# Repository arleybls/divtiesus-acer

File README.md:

# divtiesus-acer

A custom-PCB fork of **DivTIESUS** — a DivMMC-compatible SD/MMC card interface for the ZX Spectrum.

This fork is a **board re-layout only**: the CPLD firmware and its pinout are unchanged from
upstream, so the existing logic runs on the new PCB without modification.

## Lineage

| Stage | Author | Repo |
|-------|--------|------|
| Original DivTIESUS | Miguel Ángel Rodríguez Jodar (*mcleod-ideafix*) | https://github.com/mcleod-ideafix/divtiesus |
| KiCad redesign ("maple" edition) | anarsoul | https://github.com/anarsoul/divtiesus_maple |
| This fork (`divtiesus-acer`) | — | custom PCB re-layout based on the maple edition |

## What is unchanged from upstream

The entire `cpld/` directory matches the maple edition:

- Same Verilog sources: `tld_divtiesus.v`, `divmmc_mcleod.v`, `modo.v`, `segajoy.v`, `tres_e.v`,
  `uart.v`, `zxunoregs.v`, `zxunouart.v`
- Same `config.vh` and `Makefile`
- Same `tld_divtiesus.qsf` pin map — target device **Altera MAX II `EPM240T100C5`**

Inherited feature set:

- DivMMC-compatible interface with 8 KiB EEPROM and 128 KiB or 512 KiB RAM
- Automatic Spectrum model detection (no jumpers/switches)
- 24 MHz independent clock
- microSD card support with activity LED
- NMI and RESET buttons (file browser access)
- Optional ZX-Uno-compatible UART for WiFi (115200 baud)
- Kempston joystick interface (Atari and Sega controllers)
- Soft +3E feature removed (as in the maple edition)

## License

GPLv3, inherited from the upstream sources (see the GPL headers in `cpld/tld_divtiesus.v` and the
ZX-Uno notice in `cpld/config.vh`).

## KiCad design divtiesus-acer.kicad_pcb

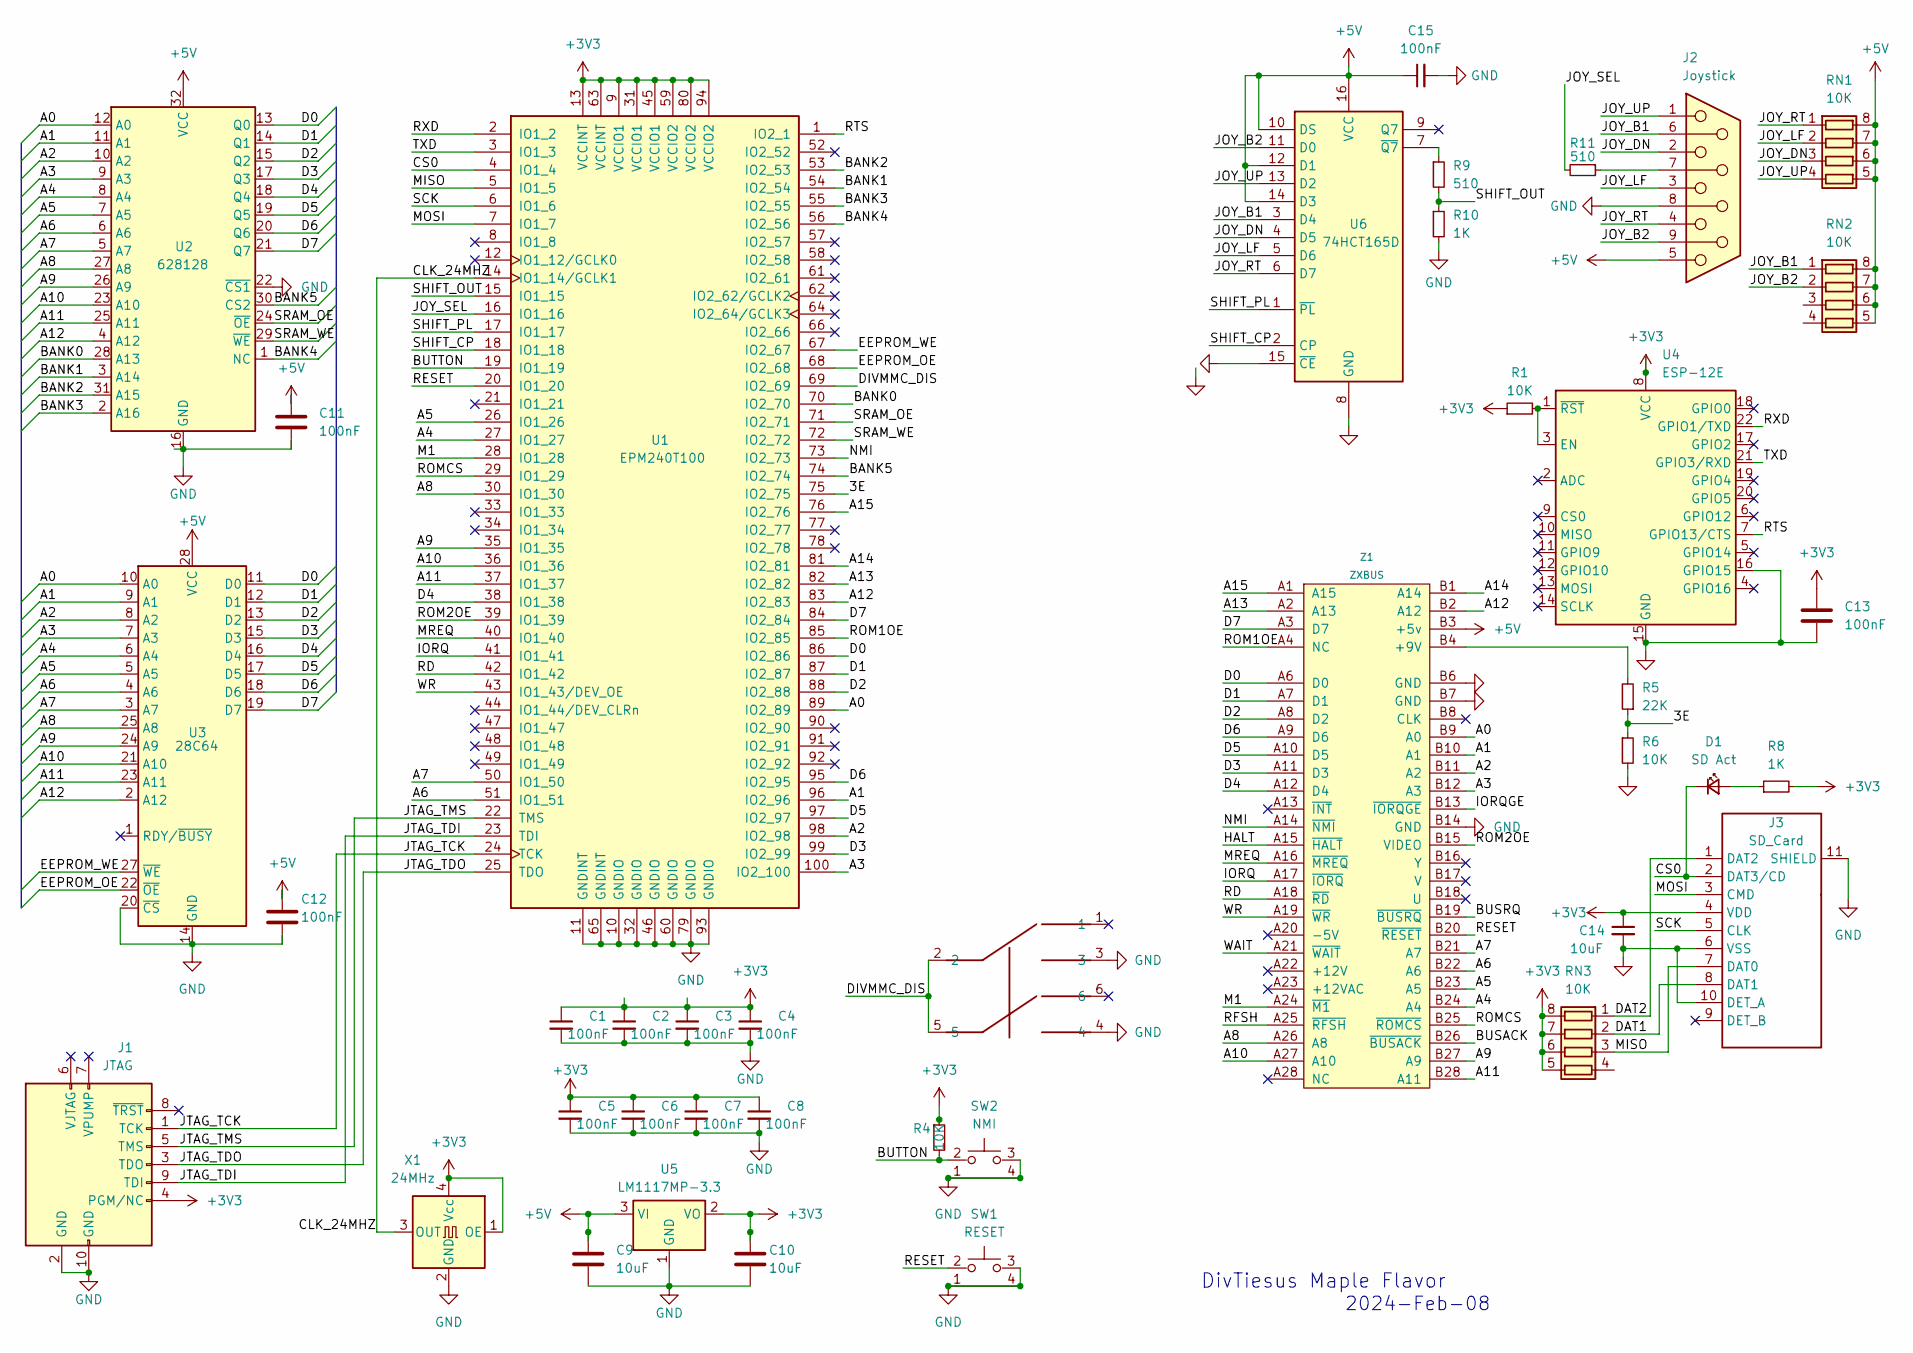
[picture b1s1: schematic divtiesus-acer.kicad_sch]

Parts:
C1, C2, C3, C4, C5, C6, C7, C8, C11, C12, C13, C15: 100nF; C_0603_1608Metric
C9, C10, C14: 10uF; C_0805_2012Metric
D1: SD Act; LED_0805_2012Metric
J1: JTAG; IDC-Header_2x05_P2.54mm_Vertical
J2: Joystick; DSUB-9_Male_Horizontal_P2.77x2.84mm_EdgePinOffset9.90mm_Hou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
J3: SD_Card; microSD_HC_Hirose_DM3D-SF; PARTREV AX6
JUMPER_E2: SWITCH_SMD_6PIN; SWICTH_SMD_6P
R1, R4, R6: 10K; R_0603_1608Metric
R5: 22K; R_0603_1608Metric
R8, R10: 1K; R_0603_1608Metric
R9, R11: 510; R_0603_1608Metric
RN1, RN2, RN3: 10K; R_Array_Convex_4x0603
SW1: RESET; SW_Tactile_SPST_Angled_PTS645Vx58-2LFS
SW2: NMI; SW_Tactile_SPST_Angled_PTS645Vx58-2LFS
U1: EPM240T100; TQFP-100_14x14mm_P0.5mm
U2: 628128; SSOP-32_11.305x20.495mm_P1.27mm
U3: 28C64; SOIC-28W_7.5x17.9mm_P1.27mm
U4: ESP-12E
U5: LM1117MP-3.3; SOT-223-3_TabPin2
U6: 74HCT165D; SOIC-16_3.9x9.9mm_P1.27mm
X1: 24MHz; Oscillator_SMD_SeikoEpson_SG8002CE-4Pin_3.2x2.5mm
Z1: ZXBUS; CONECTOR_SIMPLE_CARA

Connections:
+3V3: C1.1, C2.1, C3.1, C4.1, C5.1, C6.1, C7.1, C8.1, C10.1, C13.1, C14.1, J1.4 (PGM/NC), J3.4 (VDD), R1.1, R4.1, R8.2, RN3.5 (R4.2), RN3.6 (R3.2), RN3.7 (R2.2), RN3.8 (R1.2), U1.9 (VCCIO1), U1.13 (VCCINT), U1.31 (VCCIO1), U1.45 (VCCIO1), U1.59 (VCCIO2), U1.63 (VCCINT), U1.80 (VCCIO2), U1.94 (VCCIO2), U4.8 (VCC), U5.2 (VO), X1.1 (OE), X1.4 (Vcc)
+5V: C9.1, C11.1, C12.1, C15.1, J2.5, RN1.5 (R4.2), RN1.6 (R3.2), RN1.7 (R2.2), RN1.8 (R1.2), RN2.5 (R4.2), RN2.6 (R3.2), RN2.7 (R2.2), RN2.8 (R1.2), U2.32 (VCC), U3.28 (VCC), U5.3 (VI), U6.10 (DS), U6.12 (D1), U6.14 (D3), U6.16 (VCC), Z1.B3 (+5v)
/3E: R5.1, R6.1, U1.75 (IO2_75)
/A0: U1.89 (IO2_89), U2.12 (A0), U3.10 (A0), Z1.B9 (A0)
/A1: U1.96 (IO2_96), U2.11 (A1), U3.9 (A1), Z1.B10 (A1)
/A2: U1.98 (IO2_98), U2.10 (A2), U3.8 (A2), Z1.B11 (A2)
/A3: U1.100 (IO2_100), U2.9 (A3), U3.7 (A3), Z1.B12 (A3)
/A4: U1.27 (IO1_27), U2.8 (A4), U3.6 (A4), Z1.B24 (A4)
/A5: U1.26 (IO1_26), U2.7 (A5), U3.5 (A5), Z1.B23 (A5)
/A6: U1.51 (IO1_51), U2.6 (A6), U3.4 (A6), Z1.B22 (A6)
/A7: U1.50 (IO1_50), U2.5 (A7), U3.3 (A7), Z1.B21 (A7)
/A8: U1.30 (IO1_30), U2.27 (A8), U3.25 (A8), Z1.A26 (A8)
/A9: U1.35 (IO1_35), U2.26 (A9), U3.24 (A9), Z1.B27 (A9)
/A10: U1.36 (IO1_36), U2.23 (A10), U3.21 (A10), Z1.A27 (A10)
/A11: U1.37 (IO1_37), U2.25 (A11), U3.23 (A11), Z1.B28 (A11)
/A12: U1.83 (IO2_83), U2.4 (A12), U3.2 (A12), Z1.B2 (A12)
/A13: U1.82 (IO2_82), Z1.A2 (A13)
/A14: U1.81 (IO2_81), Z1.B1 (A14)
/A15: U1.76 (IO2_76), Z1.A1 (A15)
/BANK0: U1.70 (IO2_70), U2.28 (A13)
/BANK1: U1.54 (IO2_54), U2.3 (A14)
/BANK2: U1.53 (IO2_53), U2.31 (A15)
/BANK3: U1.55 (IO2_55), U2.2 (A16)
/BANK4: U1.56 (IO2_56), U2.1 (NC)
/BANK5: U1.74 (IO2_74), U2.30 (CS2)
/BUSACK: Z1.B26 (~BUSACK)
/BUSRQ: Z1.B19 (~BUSRQ)
/BUTTON: R4.2, SW2.2, U1.19 (IO1_19)
/CLK_24MHZ: U1.14 (IO1_14/GCLK1), X1.3 (OUT)
/CS0: D1.1 (K), J3.2 (DAT3/CD), U1.4 (IO1_4)
/D0: U1.86 (IO2_86), U2.13 (Q0), U3.11 (D0), Z1.A6 (D0)
/D1: U1.87 (IO2_87), U2.14 (Q1), U3.12 (D1), Z1.A7 (D1)
/D2: U1.88 (IO2_88), U2.15 (Q2), U3.13 (D2), Z1.A8 (D2)
/D3: U1.99 (IO2_99), U2.17 (Q3), U3.15 (D3), Z1.A11 (D3)
/D4: U1.38 (IO1_38), U2.18 (Q4), U3.16 (D4), Z1.A12 (D4)
/D5: U1.97 (IO2_97), U2.19 (Q5), U3.17 (D5), Z1.A10 (D5)
/D6: U1.95 (IO2_95), U2.20 (Q6), U3.18 (D6), Z1.A9 (D6)
/D7: U1.84 (IO2_84), U2.21 (Q7), U3.19 (D7), Z1.A3 (D7)
/DAT1: J3.8 (DAT1), RN3.2 (R2.1)
/DAT2: J3.1 (DAT2), RN3.1 (R1.1)
/DIVMMC_DIS: JUMPER_E2.2, JUMPER_E2.5, U1.69 (IO2_69)
/EEPROM_OE: U1.68 (IO2_68), U3.22 (~OE)
/EEPROM_WE: U1.67 (IO2_67), U3.27 (~WE)
/HALT: Z1.A15 (~HALT)
/IORQ: U1.41 (IO1_41), Z1.A17 (~IORQ)
/IORQGE: Z1.B13 (~IORQGE)
/JOY_B1: J2.6, RN2.1 (R1.1), U6.3 (D4)
/JOY_B2: J2.9, RN2.2 (R2.1), U6.11 (D0)
/JOY_DN: J2.2, RN1.3 (R3.1), U6.4 (D5)
/JOY_LF: J2.3, RN1.2 (R2.1), U6.5 (D6)
/JOY_RT: J2.4, RN1.1 (R1.1), U6.6 (D7)
/JOY_SEL: R11.2, U1.16 (IO1_16)
/JOY_UP: J2.1, RN1.4 (R4.1), U6.13 (D2)
/JTAG_TCK: J1.1 (TCK), U1.24 (TCK)
/JTAG_TDI: J1.9 (TDI), U1.23 (TDI)
/JTAG_TDO: J1.3 (TDO), U1.25 (TDO)
/JTAG_TMS: J1.5 (TMS), U1.22 (TMS)
/M1: U1.28 (IO1_28), Z1.A24 (~M1)
/MISO: J3.7 (DAT0), RN3.3 (R3.1), U1.5 (IO1_5)
/MOSI: J3.3 (CMD), U1.7 (IO1_7)
/MREQ: U1.40 (IO1_40), Z1.A16 (~MREQ)
/NMI: U1.73 (IO2_73), Z1.A14 (~NMI)
/RD: U1.42 (IO1_42), Z1.A18 (~RD)
/RESET: SW1.2, U1.20 (IO1_20), Z1.B20 (~RESET)
/RFSH: Z1.A25 (~RFSH)
/ROM1OE: U1.85 (IO2_85), Z1.A4 (NC)
/ROM2OE: U1.39 (IO1_39), Z1.B15 (VIDEO)
/ROMCS: U1.29 (IO1_29), Z1.B25 (~ROMCS)
/RTS: U1.1 (IO2_1), U4.7 (GPIO13/CTS)
/RXD: U1.2 (IO1_2), U4.22 (GPIO1/TXD)
/SCK: J3.5 (CLK), U1.6 (IO1_6)
/SHIFT_CP: U1.18 (IO1_18), U6.2 (CP)
/SHIFT_OUT: R9.2, R10.1, U1.15 (IO1_15)
/SHIFT_PL: U1.17 (IO1_17), U6.1 (~PL)
/SRAM_OE: U1.71 (IO2_71), U2.24 (~OE)
/SRAM_WE: U1.72 (IO2_72), U2.29 (~WE)
/TXD: U1.3 (IO1_3), U4.21 (GPIO3/RXD)
/WAIT: Z1.A21 (~WAIT)
/WR: U1.43 (IO1_43/DEV_OE), Z1.A19 (~WR)
GND: C1.2, C2.2, C3.2, C4.2, C5.2, C6.2, C7.2, C8.2, C9.2, C10.2, C11.2, C12.2, C13.2, C14.2, C15.2, J1.2 (GND), J1.10 (GND), J2.8, J3.6 (VSS), J3.10 (DET_A), J3.11 (SHIELD), JUMPER_E2.3, JUMPER_E2.4, R6.2, R10.2, SW1.1, SW1.3, SW1.4, SW2.1, SW2.3, SW2.4, U1.10 (GNDIO), U1.11 (GNDINT), U1.32 (GNDIO), U1.46 (GNDIO), U1.60 (GNDIO), U1.65 (GNDINT), U1.79 (GNDIO), U1.93 (GNDIO), U2.16 (GND), U2.22 (~CS1), U3.14 (GND), U3.20 (~CS), U4.15 (GND), U4.16 (GPIO15), U5.1 (GND), U6.8 (GND), U6.15 (~CE), X1.2 (GND), Z1.B6 (GND), Z1.B7 (GND), Z1.B14 (GND)
unnamed: D1.2 (A), R8.1
unnamed: J2.7, R11.1
unnamed: R1.2, U4.1 (~RST), U4.3 (EN)
unnamed: R9.1, U6.7 (~Q7)
unnamed: R5.2, Z1.B4 (+9V)

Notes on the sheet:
2024-Feb-08
DivTiesus Maple Flavor

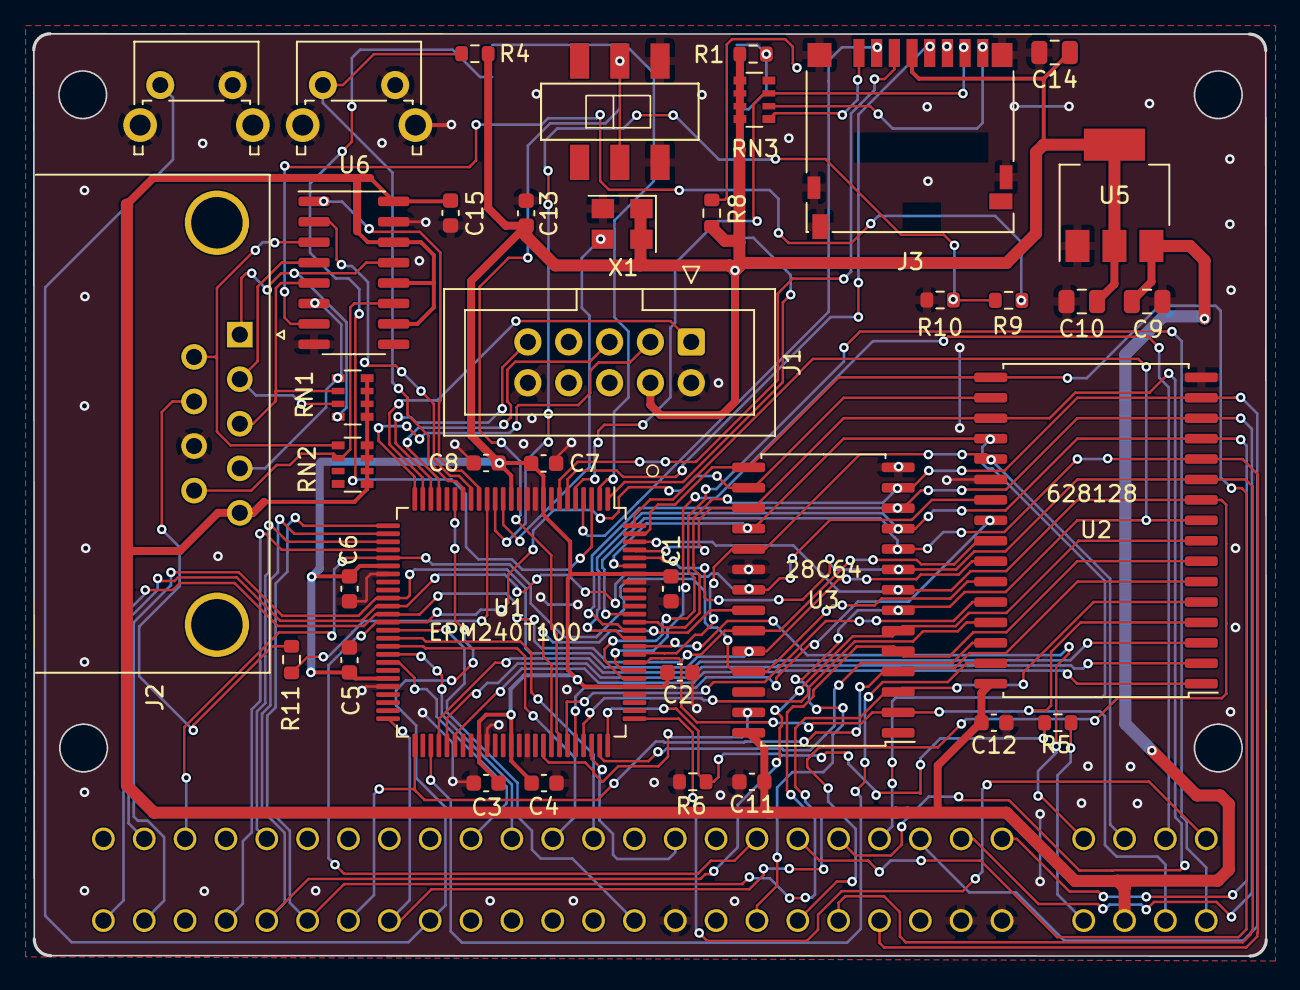
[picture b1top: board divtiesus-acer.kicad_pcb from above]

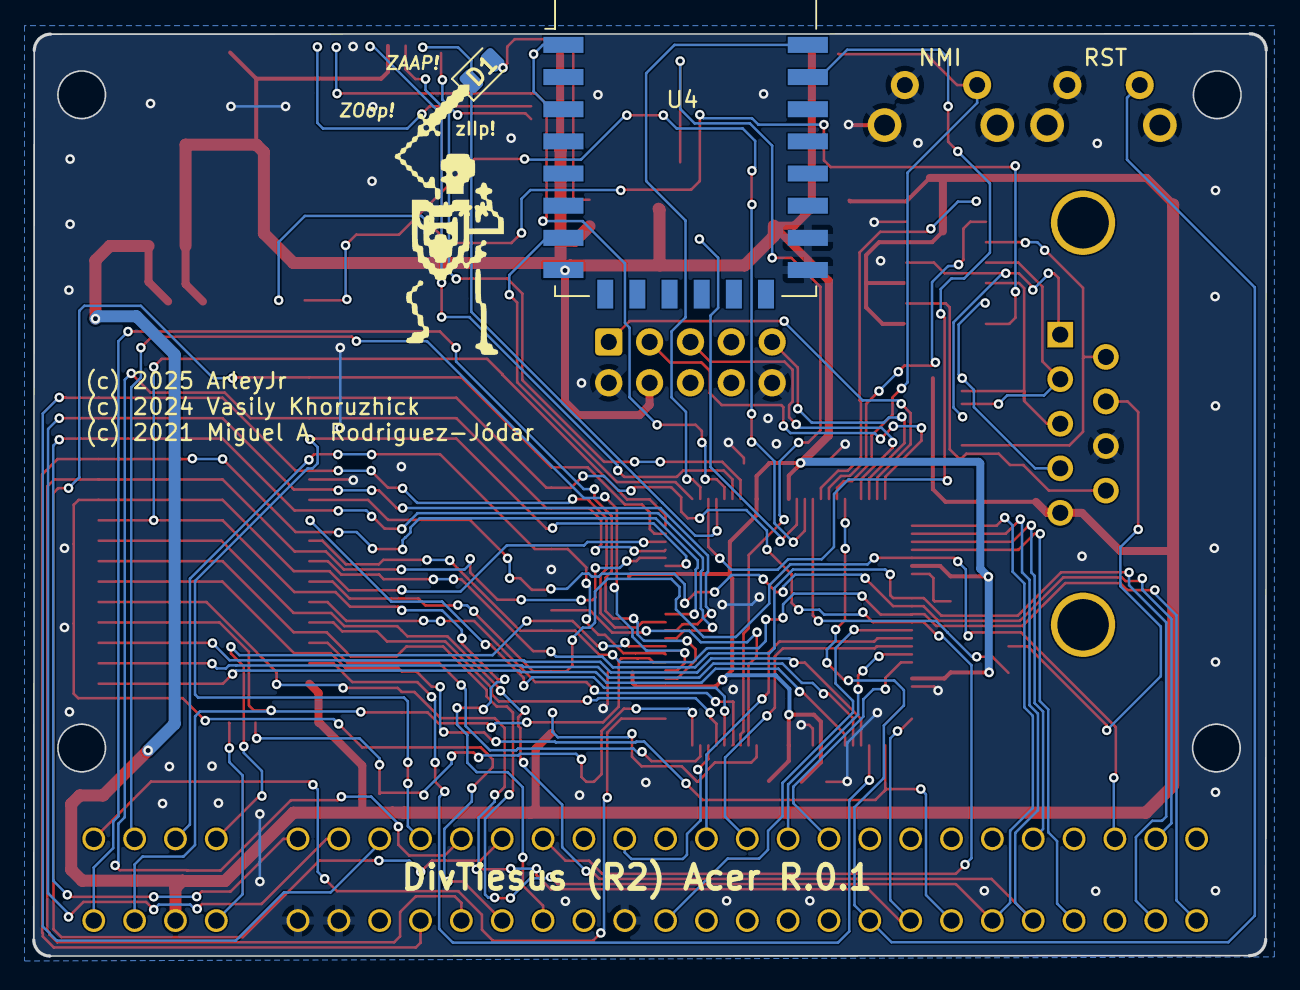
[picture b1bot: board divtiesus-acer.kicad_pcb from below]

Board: 2 copper layers, 76.6 x 57.4 mm, 41 parts (2 on the bottom side), 79 nets.

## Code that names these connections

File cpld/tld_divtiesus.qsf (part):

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set_location_assignment PIN_3 -to uart_tx
set_location_assignment PIN_1 -to uart_rts
set_location_assignment PIN_15 -to shift_q
set_location_assignment PIN_18 -to shift_cp
set_location_assignment PIN_17 -to shift_pl
set_location_assignment PIN_16 -to joy_sel
set_global_assignment -name POWER_PRESET_COOLING_SOLUTION "NO HEAT SINK WITH STILL AIR"
set_instance_assignment -name CURRENT_STRENGTH_NEW 8MA -to d[7]
set_instance_assignment -name CURRENT_STRENGTH_NEW 8MA -to d[6]
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set_global_assignment -name DEVICE_FILTER_SPEED_GRADE 5
set_global_assignment -name OPTIMIZATION_MODE BALANCED
set_instance_assignment -name WEAK_PULL_UP_RESISTOR ON -to nmi_button_n
set_location_assignment PIN_29 -to romcs
set_instance_assignment -name CURRENT_STRENGTH_NEW "MAXIMUM CURRENT" -to romcs
set_instance_assignment -name IO_STANDARD "3.3-V LVTTL" -to romcs
set_instance_assignment -name IO_STANDARD "3.3-V LVTTL" -to romoe2
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
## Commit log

2026-06-23 Initial commit: divtiesus-acer PCB redesign of DivTIESUS
2026-06-23 Remove Building the CPLD section from README
2026-06-23 Add board photo to README

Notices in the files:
cpld/tld_divtiesus.qsf:
Copyright (C) 2020  Intel Corporation. All rights reserved.
divtiesus-acer.kicad_pcb:
(c) 2025 ArleyJr
(c) 2024 Vasily Khoruzhick
(c) 2021 Miguel A. Rodriguez-Jódar
